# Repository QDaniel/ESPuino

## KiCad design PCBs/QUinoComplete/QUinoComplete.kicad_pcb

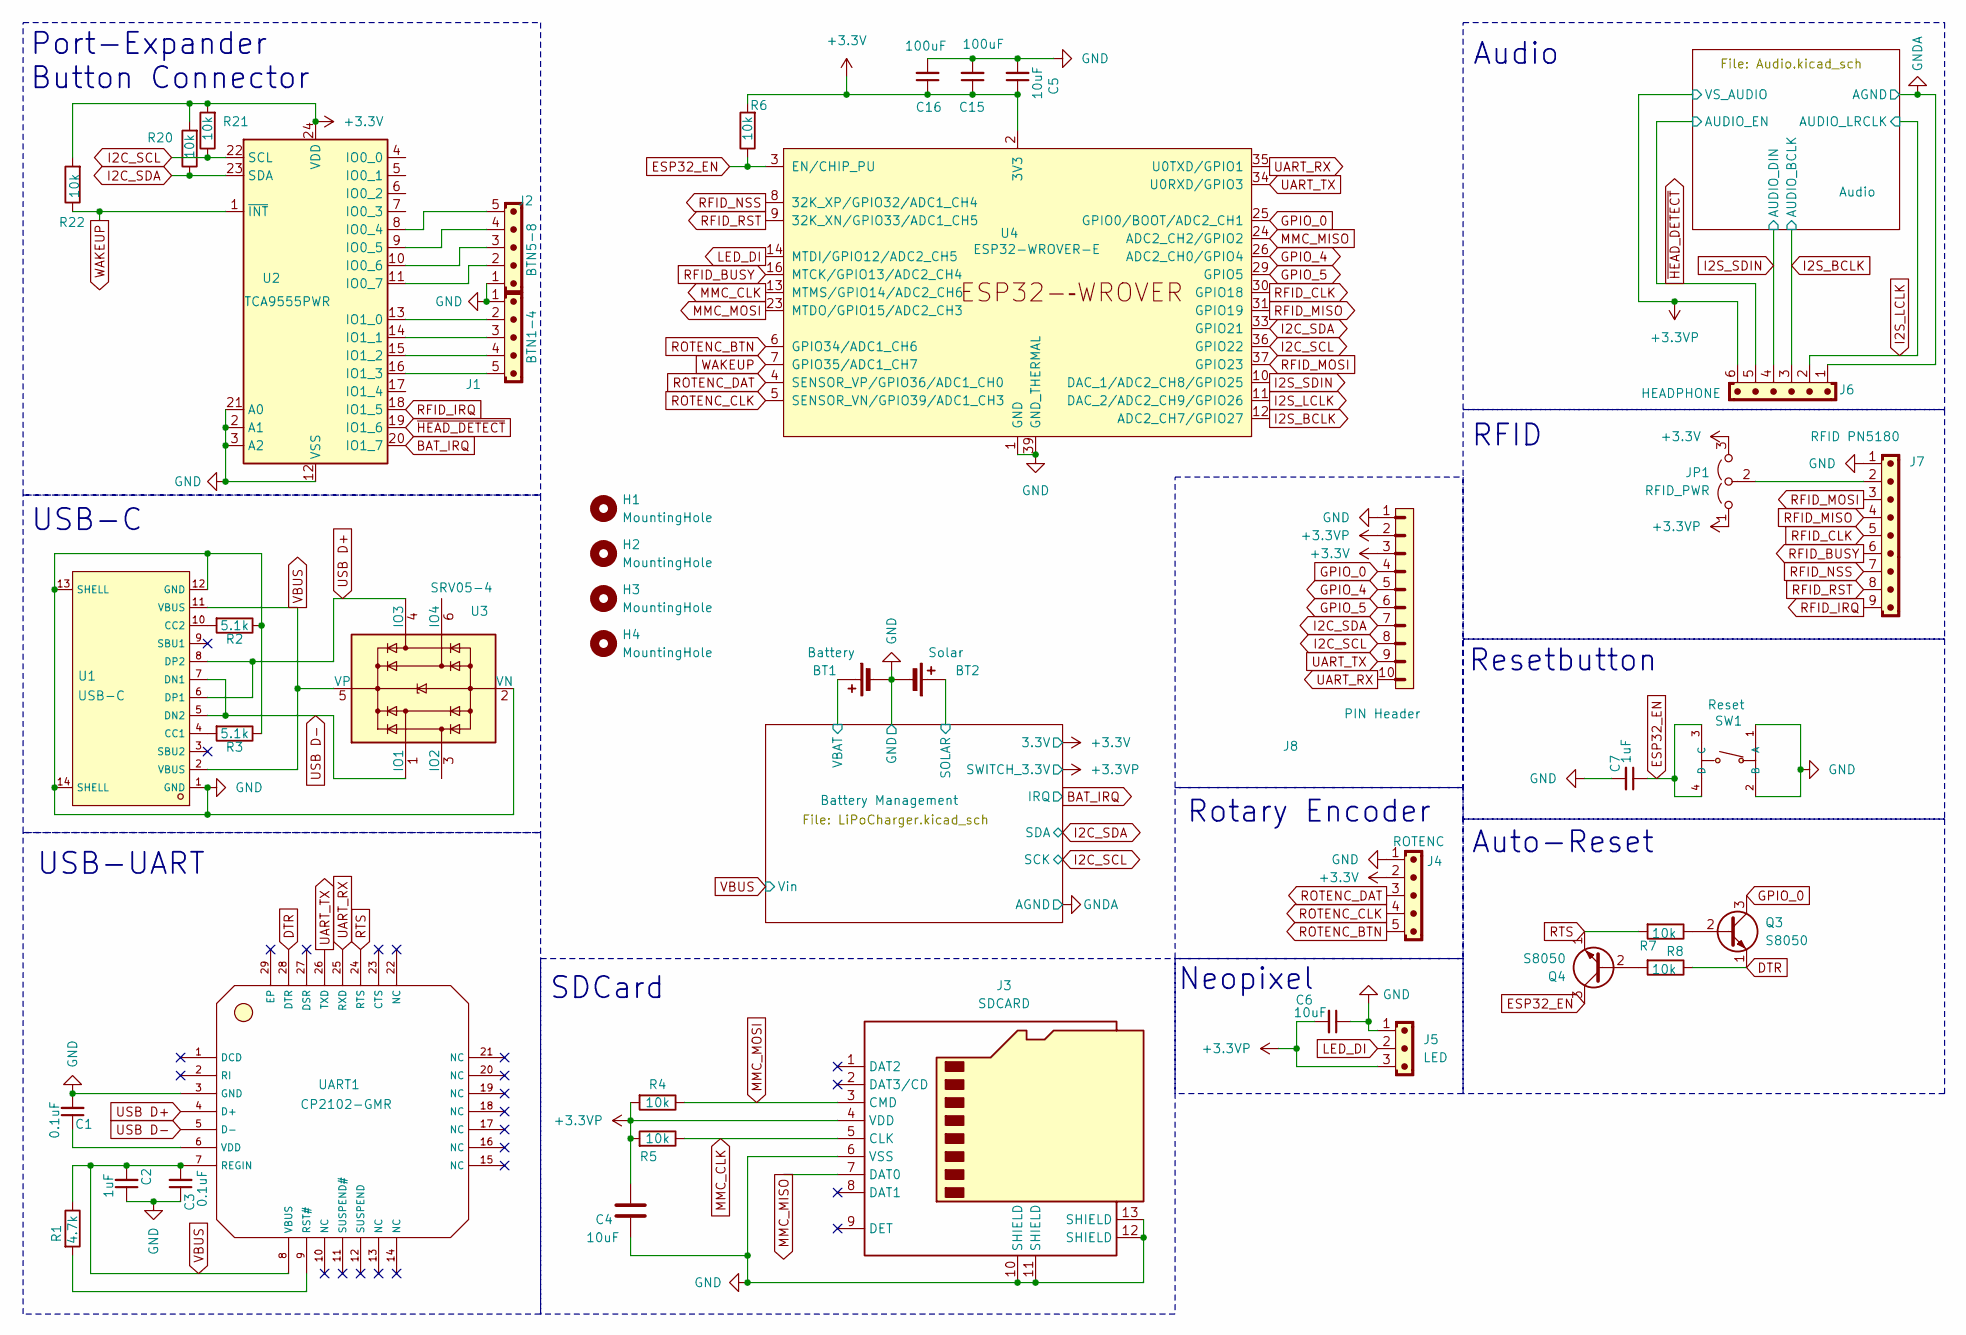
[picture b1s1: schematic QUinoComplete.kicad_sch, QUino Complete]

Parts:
BT1: Battery; JST_PH_B2B-PH-K_1x02_P2.00mm_Vertical_Reverse
BT2: Solar; JST_PH_B2B-PH-K_1x02_P2.00mm_Vertical_Reverse
C1, C3: 0.1uF; C_0402_1005Metric; JLCB-Basic 1
C2, C7: 1uF; C_0603_1608Metric; JLCB-Basic 1
C4, C5, C6: 10uF; C_0603_1608Metric; JLCB-Basic 1
C15, C16: 100uF; C_1206_3216Metric; JLCB-Basic 1
H1, H2, H3, H4: MountingHole; MountingHole_2.2mm_M2_DIN965
J1: BTN1-4; JST_EH_B5B-EH-A_1x05_P2.50mm_Vertical
J2: BTN5-8; JST_EH_B5B-EH-A_1x05_P2.50mm_Vertical
J3: SDCARD; TF-SMD_TF-CARD-H1.8; JLCB-Basic 0
J4: ROTENC; JST_EH_B5B-EH-A_1x05_P2.50mm_Vertical
J5: LED; JST_EH_B3B-EH-A_1x03_P2.50mm_Vertical
J6: HEADPHONE; JST_EH_B6B-EH-A_1x06_P2.50mm_Vertical
J7: RFID PN5180; JST_EH_B9B-EH-A_1x09_P2.50mm_Vertical
J8: PIN Header; PinHeader_1x10_P2.54mm_Vertical
JP1: RFID_PWR; SolderJumper-3_P1.3mm_Open_RoundedPad1.0x1.5mm_NumberLabels
Q3, Q4: S8050; SOT-23; LCSC C2146
R1: 4.7k; R_0603_1608Metric; LCSC C23162
R2, R3: 5.1k; R_0805_2012Metric; JLCB-Basic 1
R4, R5: 10k; R_0402_1005Metric; JLCB-Basic 1
R6, R7, R8, R20, R21, R22: 10k; R_0402_1005Metric; LCSC C25744
SW1: Reset; SW-SMD_4P-L5.1-W5.1-P3.70-LS6.5-TL_H1.5; LCSC C318884
U1: USB-C; USB-C-SMD_TYPE-C-6PIN-2MD-073; LCSC C2765186
U2: TCA9555PWR; TSSOP-24_4.4x7.8mm_P0.65mm; JLCB-Basic 0
U3: SRV05-4; SOT-23-6; LCSC C7420376
U4: ESP32-WROVER-E; LCSC C2913202
UART1: CP2102-GMR; WQFN-28_L5.0-W5.0-P0.50-BL-EP3.2; LCSC C6568

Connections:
+3.3V: C5.1, C15.1, C16.1, J4.2, J8.3, JP1.3 (B), R6.2, R20.2, R21.2, R22.2, U2.24 (VDD), U4.2 (3V3); also elsewhere on the board
+3.3VP: C4.1, C6.2, J3.4 (VDD), J5.3, J6.6, J8.2, JP1.1 (A), R4.2, R5.2; also elsewhere on the board
/Battery Management/SOLAR: BT2.1 (+); also elsewhere on the board
/Battery Management/VBAT: BT1.1 (+); also elsewhere on the board
BAT_IRQ: U2.20 (IO1_7); also elsewhere on the board
DTR: Q3.1 (E), R8.1, UART1.28 (DTR)
ESP32_EN: C7.1, Q4.3 (C), R6.1, SW1.3 (C), SW1.4 (D), U4.3 (EN/CHIP_PU)
GND: BT1.2 (-), BT2.2 (-), C1.2, C2.1, C3.1, C4.2, C5.2, C6.1, C7.2, C15.2, C16.2, J1.1, J2.1, J3.6 (VSS), J3.10 (SHIELD), J3.11 (SHIELD), J3.12 (SHIELD), J3.13 (SHIELD), J4.1, J5.1, J7.1, J8.1, R2.1, R3.1, SW1.1 (A), SW1.2 (B), U1.1 (GND), U1.12 (GND), U1.13 (SHELL), U1.14 (SHELL), U2.2 (A1), U2.3 (A2), U2.12 (VSS), U2.21 (A0), U3.2 (VN), U4.1 (GND), U4.15 (GND), U4.38 (GND), U4.39 (GND_THERMAL), UART1.3 (GND); also elsewhere on the board
GNDA: J6.1; also elsewhere on the board
GPIO_0: J8.4, Q3.3 (C), U4.25 (GPIO0/BOOT/ADC2_CH1)
GPIO_4: J8.5, U4.26 (ADC2_CH0/GPIO4)
GPIO_5: J8.6, U4.29 (GPIO5)
I2C_SCL: J8.8, R21.1, U2.22 (SCL), U4.36 (GPIO22); also elsewhere on the board
I2C_SDA: J8.7, R20.1, U2.23 (SDA), U4.33 (GPIO21); also elsewhere on the board
I2S_BCLK: J6.3, U4.12 (ADC2_CH7/GPIO27); also elsewhere on the board
I2S_LCLK: J6.2, U4.11 (DAC_2/ADC2_CH9/GPIO26); also elsewhere on the board
I2S_SDIN: J6.4, U4.10 (DAC_1/ADC2_CH8/GPIO25); also elsewhere on the board
LED_DI: J5.2, U4.14 (MTDI/GPIO12/ADC2_CH5)
MMC_CLK: J3.5 (CLK), R5.1, U4.13 (MTMS/GPIO14/ADC2_CH6)
MMC_MISO: J3.7 (DAT0), U4.24 (ADC2_CH2/GPIO2)
MMC_MOSI: J3.3 (CMD), R4.1, U4.23 (MTDO/GPIO15/ADC2_CH3)
unnamed: J7.2, JP1.2 (C)
unnamed: Q3.2 (B), R7.1
unnamed: Q4.2 (B), R8.2
unnamed: R3.2, U1.4 (CC1)
unnamed: R2.2, U1.10 (CC2)
unnamed: J2.5, U2.8 (IO0_4)
unnamed: J2.4, U2.9 (IO0_5)
unnamed: J2.3, U2.10 (IO0_6)
unnamed: J2.2, U2.11 (IO0_7)
unnamed: J1.2, U2.13 (IO1_0)
unnamed: J1.3, U2.14 (IO1_1)
unnamed: J1.4, U2.15 (IO1_2)
unnamed: J1.5, U2.16 (IO1_3)
unnamed: R1.2, UART1.9 (RST#)
unnamed: C1.1, UART1.6 (VDD)
RFID_BUSY: J7.6, U4.16 (MTCK/GPIO13/ADC2_CH4)
RFID_CLK: J7.5, U4.30 (GPIO18)
RFID_IRQ: J7.9, U2.18 (IO1_5)
RFID_MISO: J7.4, U4.31 (GPIO19)
RFID_MOSI: J7.3, U4.37 (GPIO23)
RFID_NSS: J7.7, U4.8 (32K_XP/GPIO32/ADC1_CH4)
RFID_RST: J7.8, U4.9 (32K_XN/GPIO33/ADC1_CH5)
ROTENC_BTN: J4.5, U4.6 (GPIO34/ADC1_CH6)
ROTENC_CLK: J4.4, U4.5 (SENSOR_VN/GPIO39/ADC1_CH3)
ROTENC_DAT: J4.3, U4.4 (SENSOR_VP/GPIO36/ADC1_CH0)
RTS: Q4.1 (E), R7.2, UART1.24 (RTS)
UART_RX: J8.10, U4.35 (U0TXD/GPIO1), UART1.25 (RXD)
UART_TX: J8.9, U4.34 (U0RXD/GPIO3), UART1.26 (TXD)
USB D+: U1.6 (DP1), U1.8 (DP2), U3.4 (IO3), UART1.4 (D+)
USB D-: U1.5 (DN2), U1.7 (DN1), U3.1 (IO1), UART1.5 (D-)
VBUS: C2.2, C3.2, R1.1, U1.2 (VBUS), U1.11 (VBUS), U3.5 (VP), UART1.7 (REGIN), UART1.8 (VBUS); also elsewhere on the board
WAKEUP: R22.1, U2.1 (~INT), U4.7 (GPIO35/ADC1_CH7)
~HEAD_DETECT: J6.5, U2.19 (IO1_6); also elsewhere on the board

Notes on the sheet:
Port-Expander Button Connector
USB-UART
SDCard
RFID
USB-C
Resetbutton
Auto-Reset
Neopixel
Rotary Encoder
Audio

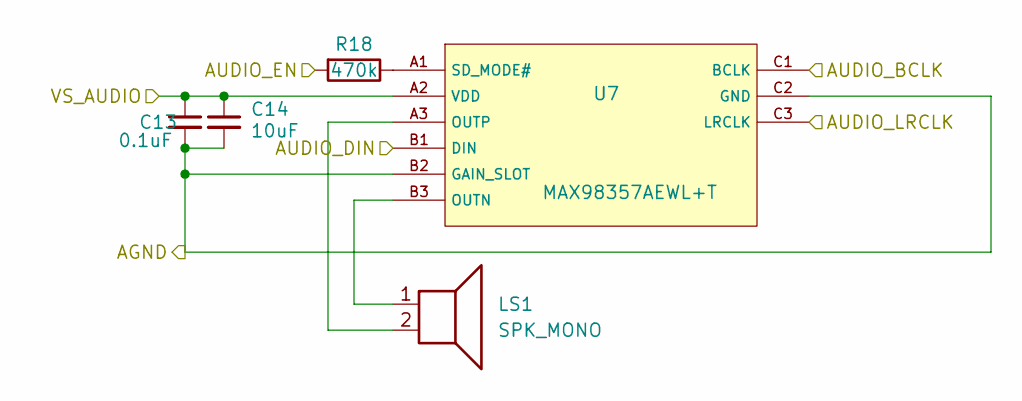
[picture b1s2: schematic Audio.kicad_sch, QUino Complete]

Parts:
C13: 0.1uF; C_0402_1005Metric; JLCB-Basic 1
C14: 10uF; C_0603_1608Metric; JLCB-Basic 1
LS1: SPK_MONO; JST_EH_B2B-EH-A_1x02_P2.50mm_Vertical
R18: 470k; R_0603_1608Metric; JLCB-Basic 1
U7: MAX98357AEWL+T; WLP-9_L1.4-W1.3-P0.40-R3-C3-BR; LCSC C2682619

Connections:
+3.3VP: C13.1, C14.1, U7.A2 (VDD); also elsewhere on the board
GNDA: C13.2, C14.2, U7.B2 (GAIN_SLOT), U7.C2 (GND); also elsewhere on the board
I2S_BCLK: U7.C1 (BCLK); also elsewhere on the board
I2S_LCLK: U7.C3 (LRCLK); also elsewhere on the board
I2S_SDIN: U7.B1 (DIN); also elsewhere on the board
unnamed: LS1.1, U7.B3 (OUTN)
unnamed: LS1.2, U7.A3 (OUTP)
unnamed: R18.1, U7.A1 (SD_MODE#)
~HEAD_DETECT: R18.2; also elsewhere on the board

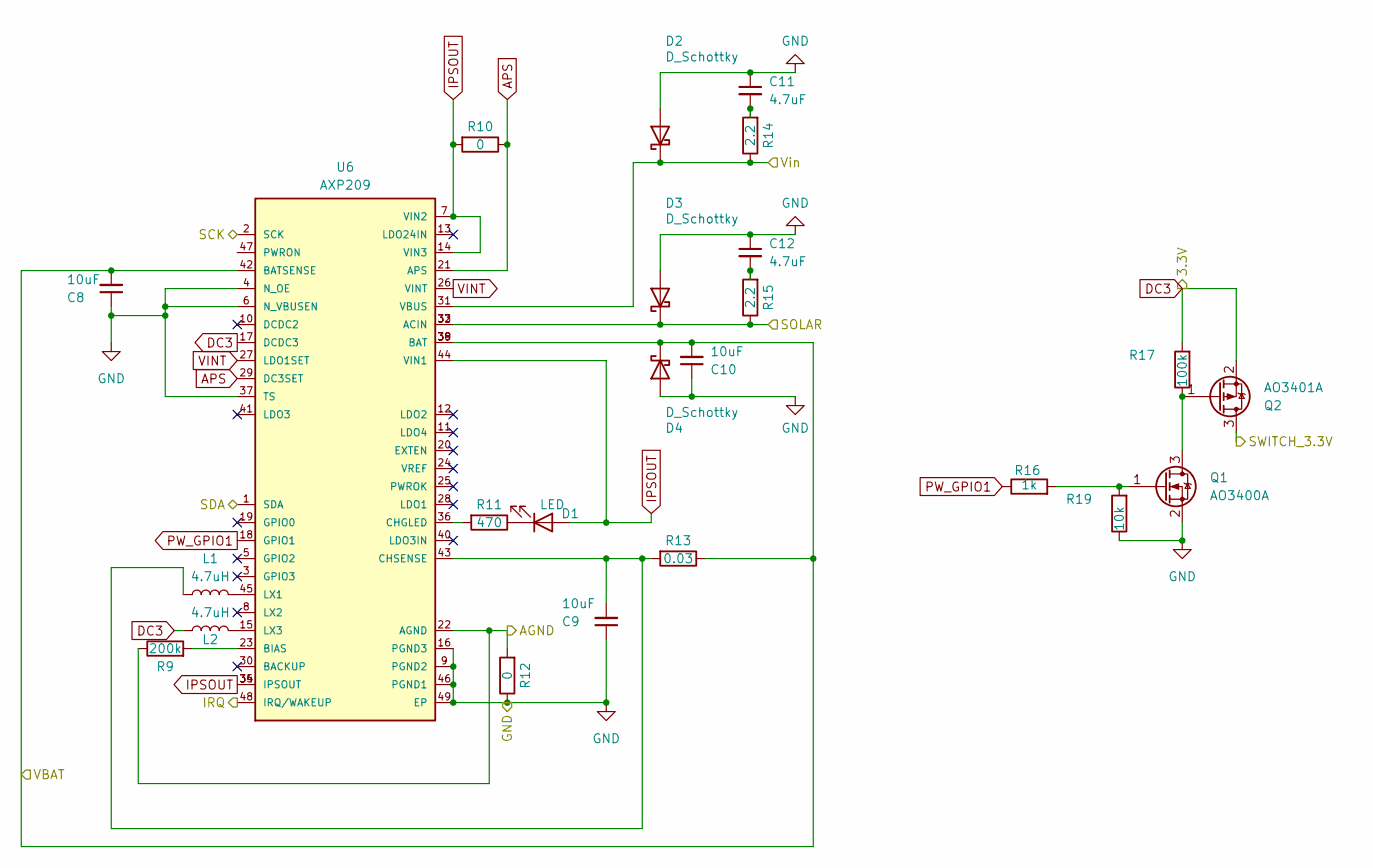
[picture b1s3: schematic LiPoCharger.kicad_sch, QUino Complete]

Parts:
C8, C9, C10: 10uF; C_0603_1608Metric; JLCB-Basic 1
C11, C12: 4.7uF; C_0402_1005Metric; JLCB-Basic 1
D1: LED; D_0603_1608Metric; JLCB-Basic 1
D2, D3, D4: D_Schottky; D_SMA; JLCB-Basic 1
L1, L2: 4.7uH; IND-SMD_L2.5-W2.0-VLS252012CX-150M; JLCB-Basic 0
Q1: AO3400A; SOT-23; LCSC C20917
Q2: AO3401A; SOT-23; LCSC C15127
R9: 200k; R_0402_1005Metric; JLCB-Basic 1
R10, R12: 0; R_1206_3216Metric; JLCB-Basic 1
R11: 470; R_0402_1005Metric; JLCB-Basic 1
R13: 0.03; R_0805_2012Metric; JLCB-Basic 0
R14, R15: 2.2; R_0603_1608Metric; JLCB-Basic 1
R16: 1k; R_0402_1005Metric; LCSC C11702
R17: 100k; R_0402_1005Metric; LCSC C25741
R19: 10k; R_0402_1005Metric; LCSC C25744
U6: AXP209; QFN40P600X600X80-49N; LCSC C2997895

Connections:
+3.3V: L2.1, Q2.2 (S), R17.2, U6.17 (DCDC3); also elsewhere on the board
+3.3VP: Q2.3 (D); also elsewhere on the board
/Battery Management/SOLAR: D3.1 (K), R15.1, U6.32 (ACIN), U6.33 (ACIN); also elsewhere on the board
/Battery Management/VBAT: C8.2, C10.2, D4.1 (K), R13.1, U6.38 (BAT), U6.39 (BAT), U6.42 (BATSENSE); also elsewhere on the board
APS: R10.1, U6.21 (APS), U6.29 (DC3SET)
BAT_IRQ: U6.48 (IRQ/WAKEUP); also elsewhere on the board
GND: C8.1, C9.1, C10.1, C11.1, C12.1, D2.2 (A), D3.2 (A), D4.2 (A), Q1.2 (S), R12.1, R19.1, U6.4 (N_OE), U6.6 (N_VBUSEN), U6.9 (PGND2), U6.16 (PGND3), U6.37 (TS), U6.46 (PGND1), U6.49 (EP); also elsewhere on the board
GNDA: R9.1, R12.2, U6.22 (AGND); also elsewhere on the board
I2C_SCL: U6.2 (SCK); also elsewhere on the board
I2C_SDA: U6.1 (SDA); also elsewhere on the board
IPSOUT: D1.2 (A), R10.2, U6.7 (VIN2), U6.14 (VIN3), U6.34 (IPSOUT), U6.35 (IPSOUT), U6.44 (VIN1)
unnamed: C11.2, R14.2
unnamed: C12.2, R15.2
unnamed: D1.1 (K), R11.1
unnamed: Q1.3 (D), Q2.1 (G), R17.1
unnamed: Q1.1 (G), R16.2, R19.2
unnamed: R9.2, U6.23 (BIAS)
unnamed: R11.2, U6.36 (CHGLED)
unnamed: C9.2, L1.1, R13.2, U6.43 (CHSENSE)
unnamed: L1.2, U6.45 (LX1)
unnamed: L2.2, U6.15 (LX3)
PW_GPIO1: R16.1, U6.18 (GPIO1)
VBUS: D2.1 (K), R14.1, U6.31 (VBUS); also elsewhere on the board
VINT: U6.26 (VINT), U6.27 (LDO1SET)

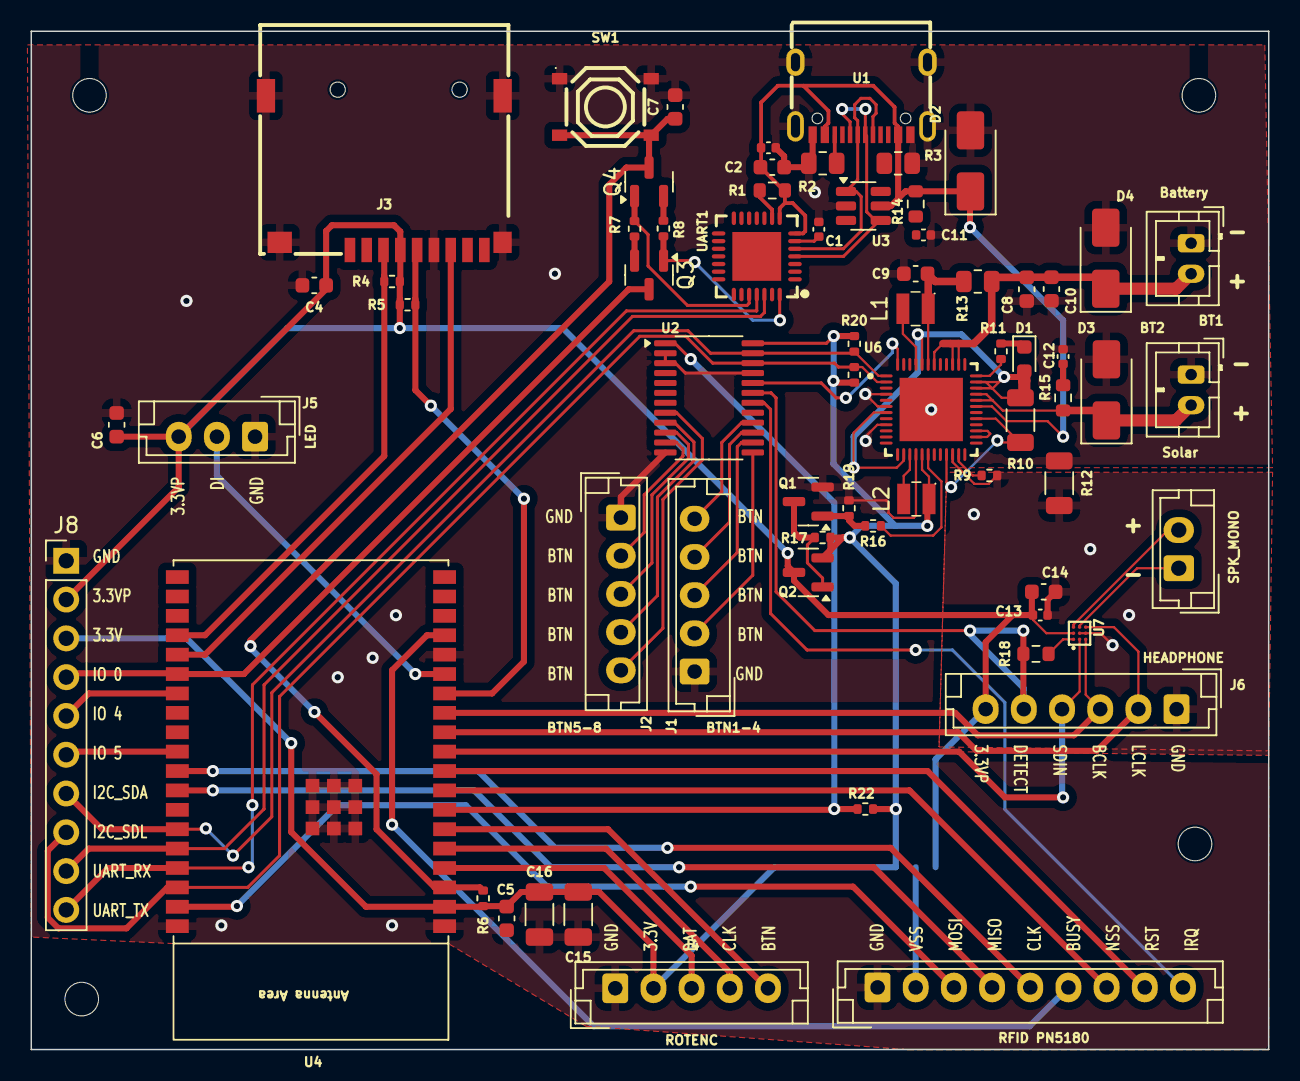
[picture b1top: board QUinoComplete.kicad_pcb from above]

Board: 2 copper layers, 81.0 x 66.7 mm, 72 parts (1 on the bottom side), 71 nets.

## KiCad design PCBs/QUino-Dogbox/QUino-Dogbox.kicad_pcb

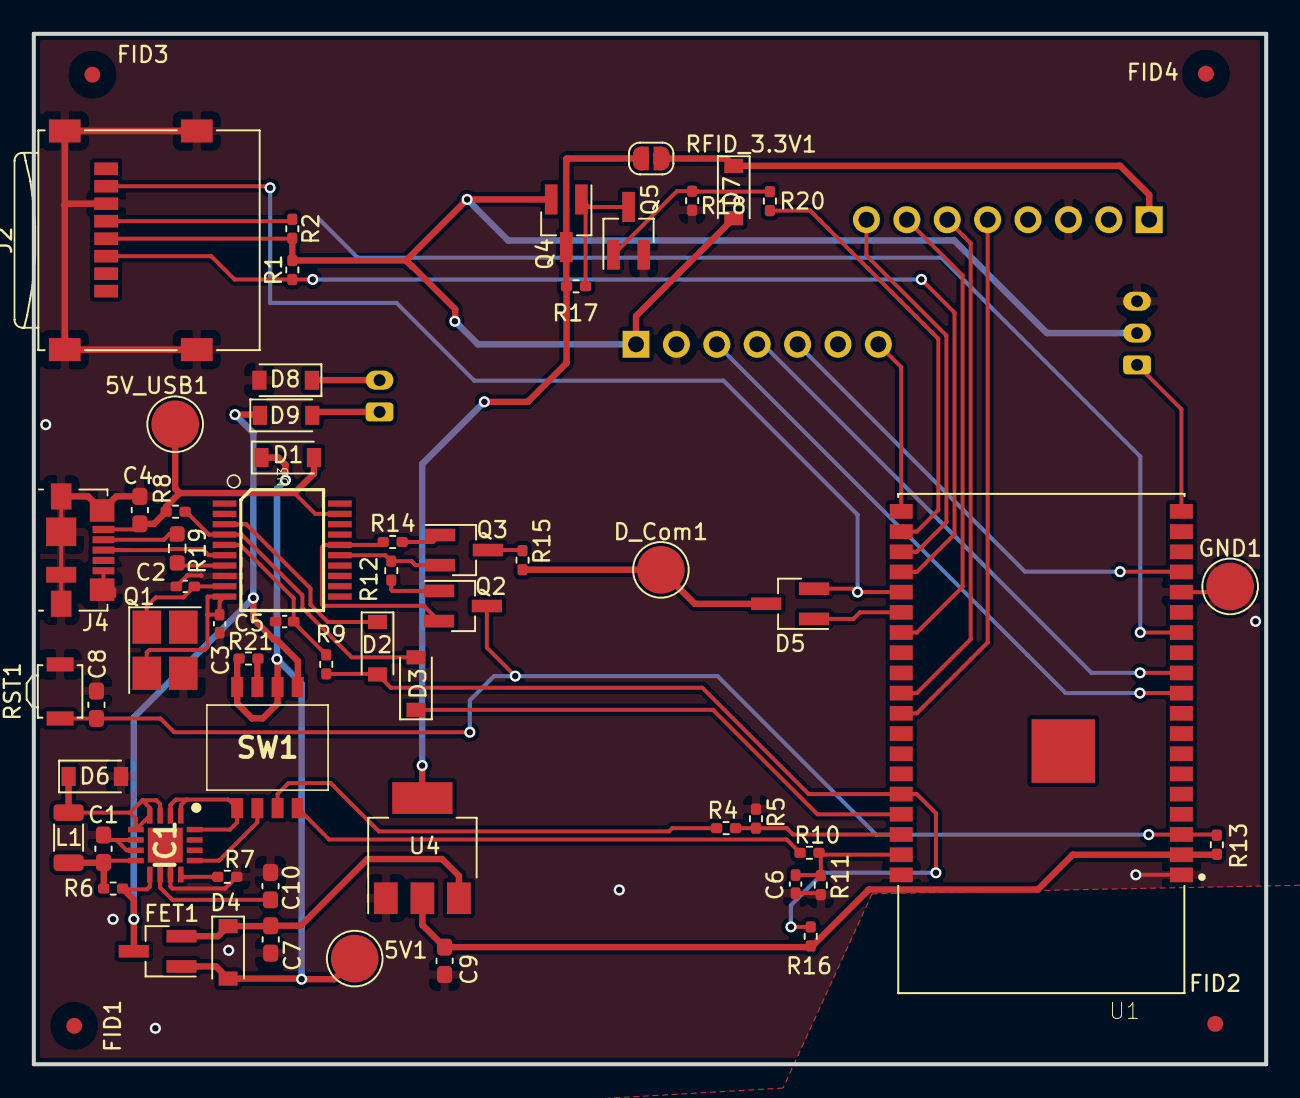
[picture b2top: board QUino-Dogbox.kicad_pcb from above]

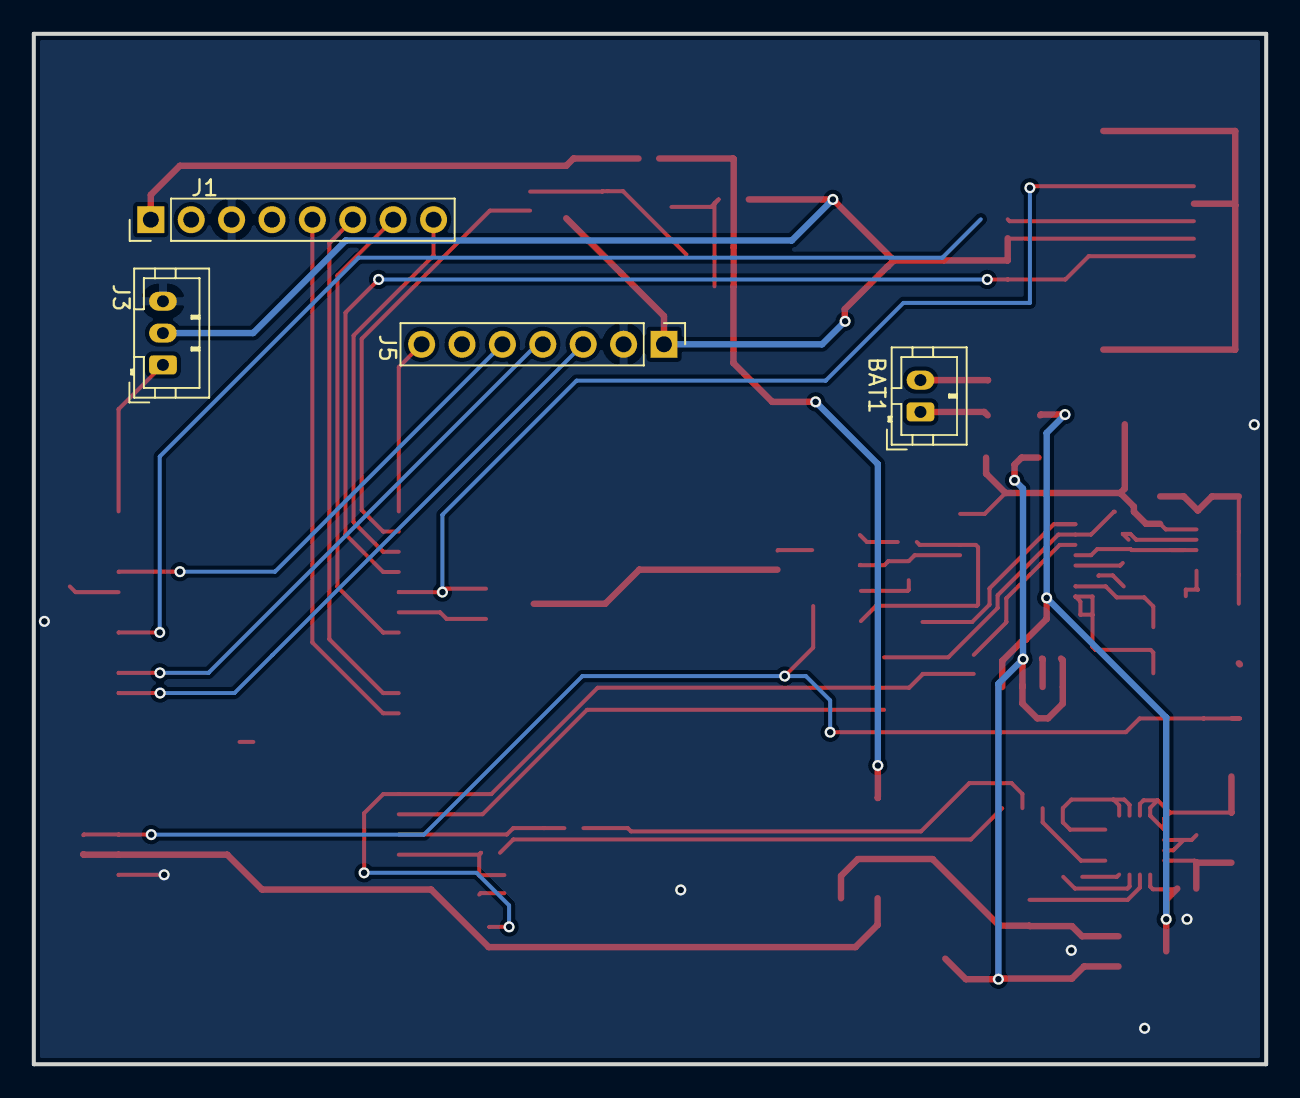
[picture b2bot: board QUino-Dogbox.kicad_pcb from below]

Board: 2 copper layers, 77.5 x 64.8 mm, 67 parts (4 on the bottom side), 54 nets.

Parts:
5V1, 5V_USB1: TESTPAD; TestPoint_Pad_D3.0mm
BAT1: DW02S; JST_PH_B2B-PH-K_1x02_P2.00mm_Vertical
C1: 10uF/C0603; C_0603_1608Metric_Pad1.08x0.95mm_HandSolder
C2, C3: 27pF/50V/5%/C0G/C0402; C_0402_1005Metric_Pad0.74x0.62mm_HandSolder
C4, C7, C9: 22uF/6.3V/20%/X5R/C0603; C_0603_1608Metric_Pad1.08x0.95mm_HandSolder
C5, C6: 100nF/10V/10%/X7R/C0402; C_0402_1005Metric_Pad0.74x0.62mm_HandSolder
C8: 1uF/10V/10%/X5R/C0603; C_0603_1608Metric_Pad1.08x0.95mm_HandSolder
C10: 0.1uF/C0603; C_0603_1608Metric_Pad1.08x0.95mm_HandSolder
D1, D2, D3, D4, D6, D7, D8, D9: 1N5819W/SOD123; D_SOD-123
D5: BAT54C(SOT23-3); SOT-23_Handsoldering
D_Com1: TESTPAD; TestPoint_Pad_D3.0mm
FET1: WPM2015-3/TR; SOT-23_Handsoldering
FID1, FID2, FID3, FID4: Fiducial; Fiducial_1mm_Mask3mm
GND1: TESTPAD; TestPoint_Pad_D3.0mm
IC1: TP5000-QFN16; QFN65P400X400X90-17N-D
J1: RFID RC522; PinHeader_1x08_P2.54mm_Vertical
J2: Micro_SD_Card; microSD_HC_Wuerth_693072010801
J3: Neopixel; JST_PH_B3B-PH-K_1x03_P2.00mm_Vertical
J4: USB_B_Micro; USB_Micro-B_Molex_47346-0001
J5: Conn_01x07_Male; PinHeader_1x07_P2.54mm_Vertical
L1: 4.7u; L_1206_3216Metric
Q1: Q12MHz/20pF/10ppm/4P/3.2x2.5mm; Crystal_SMD_3225-4Pin_3.2x2.5mm_HandSoldering
Q2, Q3: BC817-40(SOT23); SOT-23_Handsoldering
Q4: SI2302DS NMOS/GSD; SOT-23_Handsoldering
Q5: QBC817 NPN/BEC; SOT-23_Handsoldering
R1, R2, R8, R9, R13, R16, R17, R18, R21: 10k/R0402; R_0402_1005Metric_Pad0.72x0.64mm_HandSolder
R4: 220k/R0402; R_0402_1005Metric_Pad0.72x0.64mm_HandSolder
R5, R10, R11: 470k/R0402; R_0402_1005Metric_Pad0.72x0.64mm_HandSolder
R6, R7, R12, R14: 2.2k/R0402; R_0402_1005Metric_Pad0.72x0.64mm_HandSolder
R15: 220/R0402; R_0402_1005Metric_Pad0.72x0.64mm_HandSolder
R19: 0 /R0402; R_0603_1608Metric_Pad0.98x0.95mm_HandSolder
R20: 4,7k/R0402; R_0402_1005Metric_Pad0.72x0.64mm_HandSolder
RFID_3.3V1: Opened; SolderJumper-2_P1.3mm_Open_RoundedPad1.0x1.5mm
RST1: IT-1185AU2-160G-G-TR; SW_SPST_B3U-3000P
SW1: SW_DIP_x04; DSHP04TSS
U1: ESP32-WROVER; XCVR_ESP32-WROVER-I
U3: CH340T(SSOP20W); SSOP20-0.65-7.6X5.2MM
U4: AMS1117-3.3; SOT-223-3_TabPin2

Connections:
+3V3: C9.1, Q4.3, R13.1, R16.2, R17.2, RFID_3.3V1.1, U1.2, U4.2
+5V: 5V1.1, D1.1, D4.2, FET1.1, R21.1, SW1.2, SW1.4
/LiPoPower/5V: 5V_USB1.1, C4.1, D1.2, J4.1, R8.1, U3.19
/Sheet602F0C3C/D_Com: D5.3, D_Com1.1, R15.2
/Sheet602F0C3C/GPIO_EN: C8.1, Q2.3, R13.2, RST1.1, U1.3
/Sheet602F0C3C/UD+: J4.3, U3.6
/Sheet602F0C3C/UD-: R19.2, U3.7
/VSwitched: D7.2, J2.4, J3.2, J5.1, Q4.2, R1.2, R2.2
DAC_CLK: J5.5, U1.16
EXTPWR_SENSE: R4.1, R5.2, U1.36
GATE_PWR: R20.2, U1.21
GND: C1.2, C2.2, C3.2, C4.2, C5.2, C6.1, C7.2, C8.2, C9.2, C10.1, D6.2, D8.2, GND1.1, IC1.6, IC1.7, IC1.11, J1.3, J2.6, J2.9, J3.3, J4.5, J4.6, J5.2, Q1.3, Q5.2, R5.1, R7.2, R11.2, R18.2, RST1.2, U1.1, U1.15, U1.38, U3.8, U4.1
GPIO25_DAC_1: J5.3, U1.10
GPIO26_DAC_2: J5.4, U1.11
GPIO_0: D5.1, U1.25
GPIO_2: D5.2, J2.7, U1.24
GPIO_14: J2.5, R2.1, U1.13
GPIO_15: J2.3, R1.1, U1.23
GPIO_RX: D2.2, R9.2, R16.1, U1.34
GPIO_TX: D3.1, U1.35
HEADPHONE_JACK: J5.7, U1.20
LED_DI: J3.1, U1.19
unnamed: BAT1.1, D9.2
unnamed: BAT1.2, D8.1
unnamed: C1.1, IC1.8, L1.2, R6.1
unnamed: C2.1, Q1.1, U3.9
unnamed: C3.1, Q1.2, U3.10
unnamed: C5.1, R9.1, U3.5
unnamed: C7.1, D4.1, FET1.2, U4.3
unnamed: C10.2, IC1.10
unnamed: D2.1, U3.3
unnamed: D3.2, R8.2, U3.4
unnamed: D6.1, IC1.3, IC1.4, IC1.5, L1.1
unnamed: D7.1, J1.1, RFID_3.3V1.2
unnamed: IC1.1, IC1.2, IC1.16, SW1.5
unnamed: IC1.12, R7.1
unnamed: IC1.13, SW1.6
unnamed: J4.2, R19.1
unnamed: Q2.1, R12.2
unnamed: Q2.2, R14.1, U3.16
unnamed: Q3.1, R14.2
unnamed: Q3.2, R12.1, U3.15
unnamed: Q3.3, R15.1
unnamed: Q4.1, Q5.3, R17.1
unnamed: Q5.1, R18.1, R20.1
unnamed: R4.2, SW1.7
unnamed: R10.1, SW1.8
unnamed: R21.2, SW1.3
RFID_CLK: J1.7, U1.26
RFID_CS: J1.8, U1.22
RFID_MISO: J1.5, U1.30
RFID_MOSI: J1.6, U1.29
VBAT: D9.1, FET1.3, IC1.9, R6.2, SW1.1
VBAT_MEASURE: C6.2, R10.2, R11.1, U1.37

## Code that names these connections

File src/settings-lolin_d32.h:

#include "Arduino.h"

//######################### INFOS ####################################
/* This is a develboard-specific config-file for *Wemos Lolin D32*. Specific doesn't mean it's only working with this board.
   Lolin D32 is the successor of Lolin32 and the "little brother" of Wemos Lolin D32 pro.
   PCB: https://github.com/biologist79/ESPuino/tree/master/PCBs/Wemos%20Lolin%20D32
   Infos: https://www.wemos.cc/en/latest/d32/d32.html
   Schematics: https://www.wemos.cc/en/latest/_static/files/sch_d32_v1.0.0.pdf
   Caveats: GPIO35 (battery monitoring) can't be changed, it's built in
   Status:
    tested with 2x SPI: RC522 & SD (by biologist79)
*/


//################## GPIO-configuration ##############################
// Please note: GPIOs 34, 35, 36, 39 are input-only and don't have pullup-resistors.
// So if connecting a button to these, make sure to add a 10k-pullup-resistor for each button.
// Further infos: https://randomnerdtutorials.com/esp32-pinout-reference-gpios/
#ifdef SD_MMC_1BIT_MODE
    // uSD-card-reader (via SD-MMC 1Bit)
    //
    // SD_MMC uses fixed pins
    //  MOSI    15
    //  SCK     14
    //  MISO    2
#else
    // uSD-card-reader (via SPI)
    #define SPISD_CS                    15          // GPIO for chip select (SD)
    #ifndef SINGLE_SPI_ENABLE
        #define SPISD_MOSI              13          // GPIO for master out slave in (SD) => not necessary for single-SPI
        #define SPISD_MISO              16          // GPIO for master in slave ou (SD) => not necessary for single-SPI
        #define SPISD_SCK               14          // GPIO for clock-signal (SD) => not necessary for single-SPI
    #endif
#endif

// RFID (via SPI)
#define RST_PIN                         99          // Not necessary but has to be set anyway; so let's use a dummy-number
#define RFID_CS                         21          // GPIO for chip select (RFID)
#define RFID_MOSI                       23          // GPIO for master out slave in (RFID)
#define RFID_MISO                       19          // GPIO for master in slave out (RFID)
#define RFID_SCK                        18          // GPIO for clock-signal (RFID)

#ifdef RFID_READER_TYPE_PN5180
    #define RFID_BUSY                   16          // PN5180 BUSY PIN
    #define RFID_RST                    22          // PN5180 RESET PIN
    #define RFID_IRQ                    39          // PN5180 IRQ PIN (only needed for low power card detection)
	#define BUTTON_PIN_BITMASK          0x8000000000// 2^RFID_IRQ in hex
#endif
// I2S (DAC)
#define I2S_DOUT                        25          // Digital out (I2S)
#define I2S_BCLK                        27          // BCLK (I2S)
#define I2S_LRC                         26          // LRC (I2S)

// Rotary encoder
#define DREHENCODER_CLK                 34          // If you want to reverse encoder's direction, just switch GPIOs of CLK with DT (in software or hardware)
#define DREHENCODER_DT                  33          // Info: Lolin D32 / Lolin D32 pro 35 are using 35 for battery-voltage-monitoring!
#define DREHENCODER_BUTTON              32          // Button 4: is used to switch ESPuino on and off

// Control-buttons
#define NEXT_BUTTON                      4          // Button 1: GPIO to detect next
#define PREVIOUS_BUTTON                  2          // Button 2: GPIO to detect previous (Important: as of 19.11.2020 changed from 33 to 2; make sure to change in SD-MMC-mode)
#define PAUSEPLAY_BUTTON                 5          // Button 3: GPIO to detect pause/play
#define BUTTON_5                        99          // Button 5
#define BUTTON_6                        99          // Button 6

// (optional) Power-control
#define POWER                           17          // GPIO used to drive transistor-circuit, that switches off peripheral devices while ESP32-deepsleep

// (optional) Neopixel
#define LED_PIN                         12          // GPIO for Neopixel-signaling

// (optinal) Headphone-detection
#ifdef HEADPHONE_ADJUST_ENABLE
    #define HP_DETECT                   22          // GPIO that detects, if there's a plug in the headphone jack or not
#endif

// (optional) Monitoring of battery-voltage via ADC
#ifdef MEASURE_BATTERY_VOLTAGE
    #define VOLTAGE_READ_PIN            35          // Cannot be changed, it's built in
    float referenceVoltage = 3.30;                  // Voltage between 3.3V and GND-pin at the develboard in battery-mode (disconnect USB!)
    float offsetVoltage = 0.2;                      // If voltage measured by ESP isn't 100% accurate, you can add an correction-value here
#endif

#ifdef MEASURE_BATTERY_VOLTAGE
    uint8_t rdiv1 = 100;                            // Cannot be changed, it's built in
    uint16_t rdiv2 = 100;                           // Cannot be changed, it's built in
#endif

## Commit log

2021-02-04 Setting for use of longpress buttons for Volume
2021-02-13 Reusable Cards / Trackinfo on Cards
2021-02-14 Allow m3u Files, ignore comments
2021-02-14 Custom Button Layouts
2021-02-14 5 Buttons , Build errors
2021-02-14 Check Buttons Enabled
2021-02-15 Control buttons for Web UI
2021-02-17 New Multi Button System
2021-02-22 PCB QUino Dogbox
2021-02-22 LibName
2021-02-23 Schaltplan pdf
2021-02-26 Update ESP32 to WROVER-B
2024-12-16 Check if Power Defined
2024-12-16 RFID I2C Compile Error
2024-12-16 QUino Cloud-Manager
2024-12-18 Better ETag check ,clang , Logging
2024-12-18 clang
2024-12-18 Angabe der DL-Filenames
2024-12-18 dont save webstreams without etag
2024-12-25 Fix etag reading
2024-12-26 fix dl
2024-12-28 ArduinoJson 7
2025-01-02 Complete PCB
2025-01-18 freeing memory
2025-01-19 Better logging
